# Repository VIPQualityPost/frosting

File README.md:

Small, Nucleo-64 sized carrier for icesugar pro and colorlight i9 FPGA development boards. I designed this in order to be able to use the handful of Arduino and Morpho shields I have with these dev kits to avoid needing to use weird PMODS or breadboards.

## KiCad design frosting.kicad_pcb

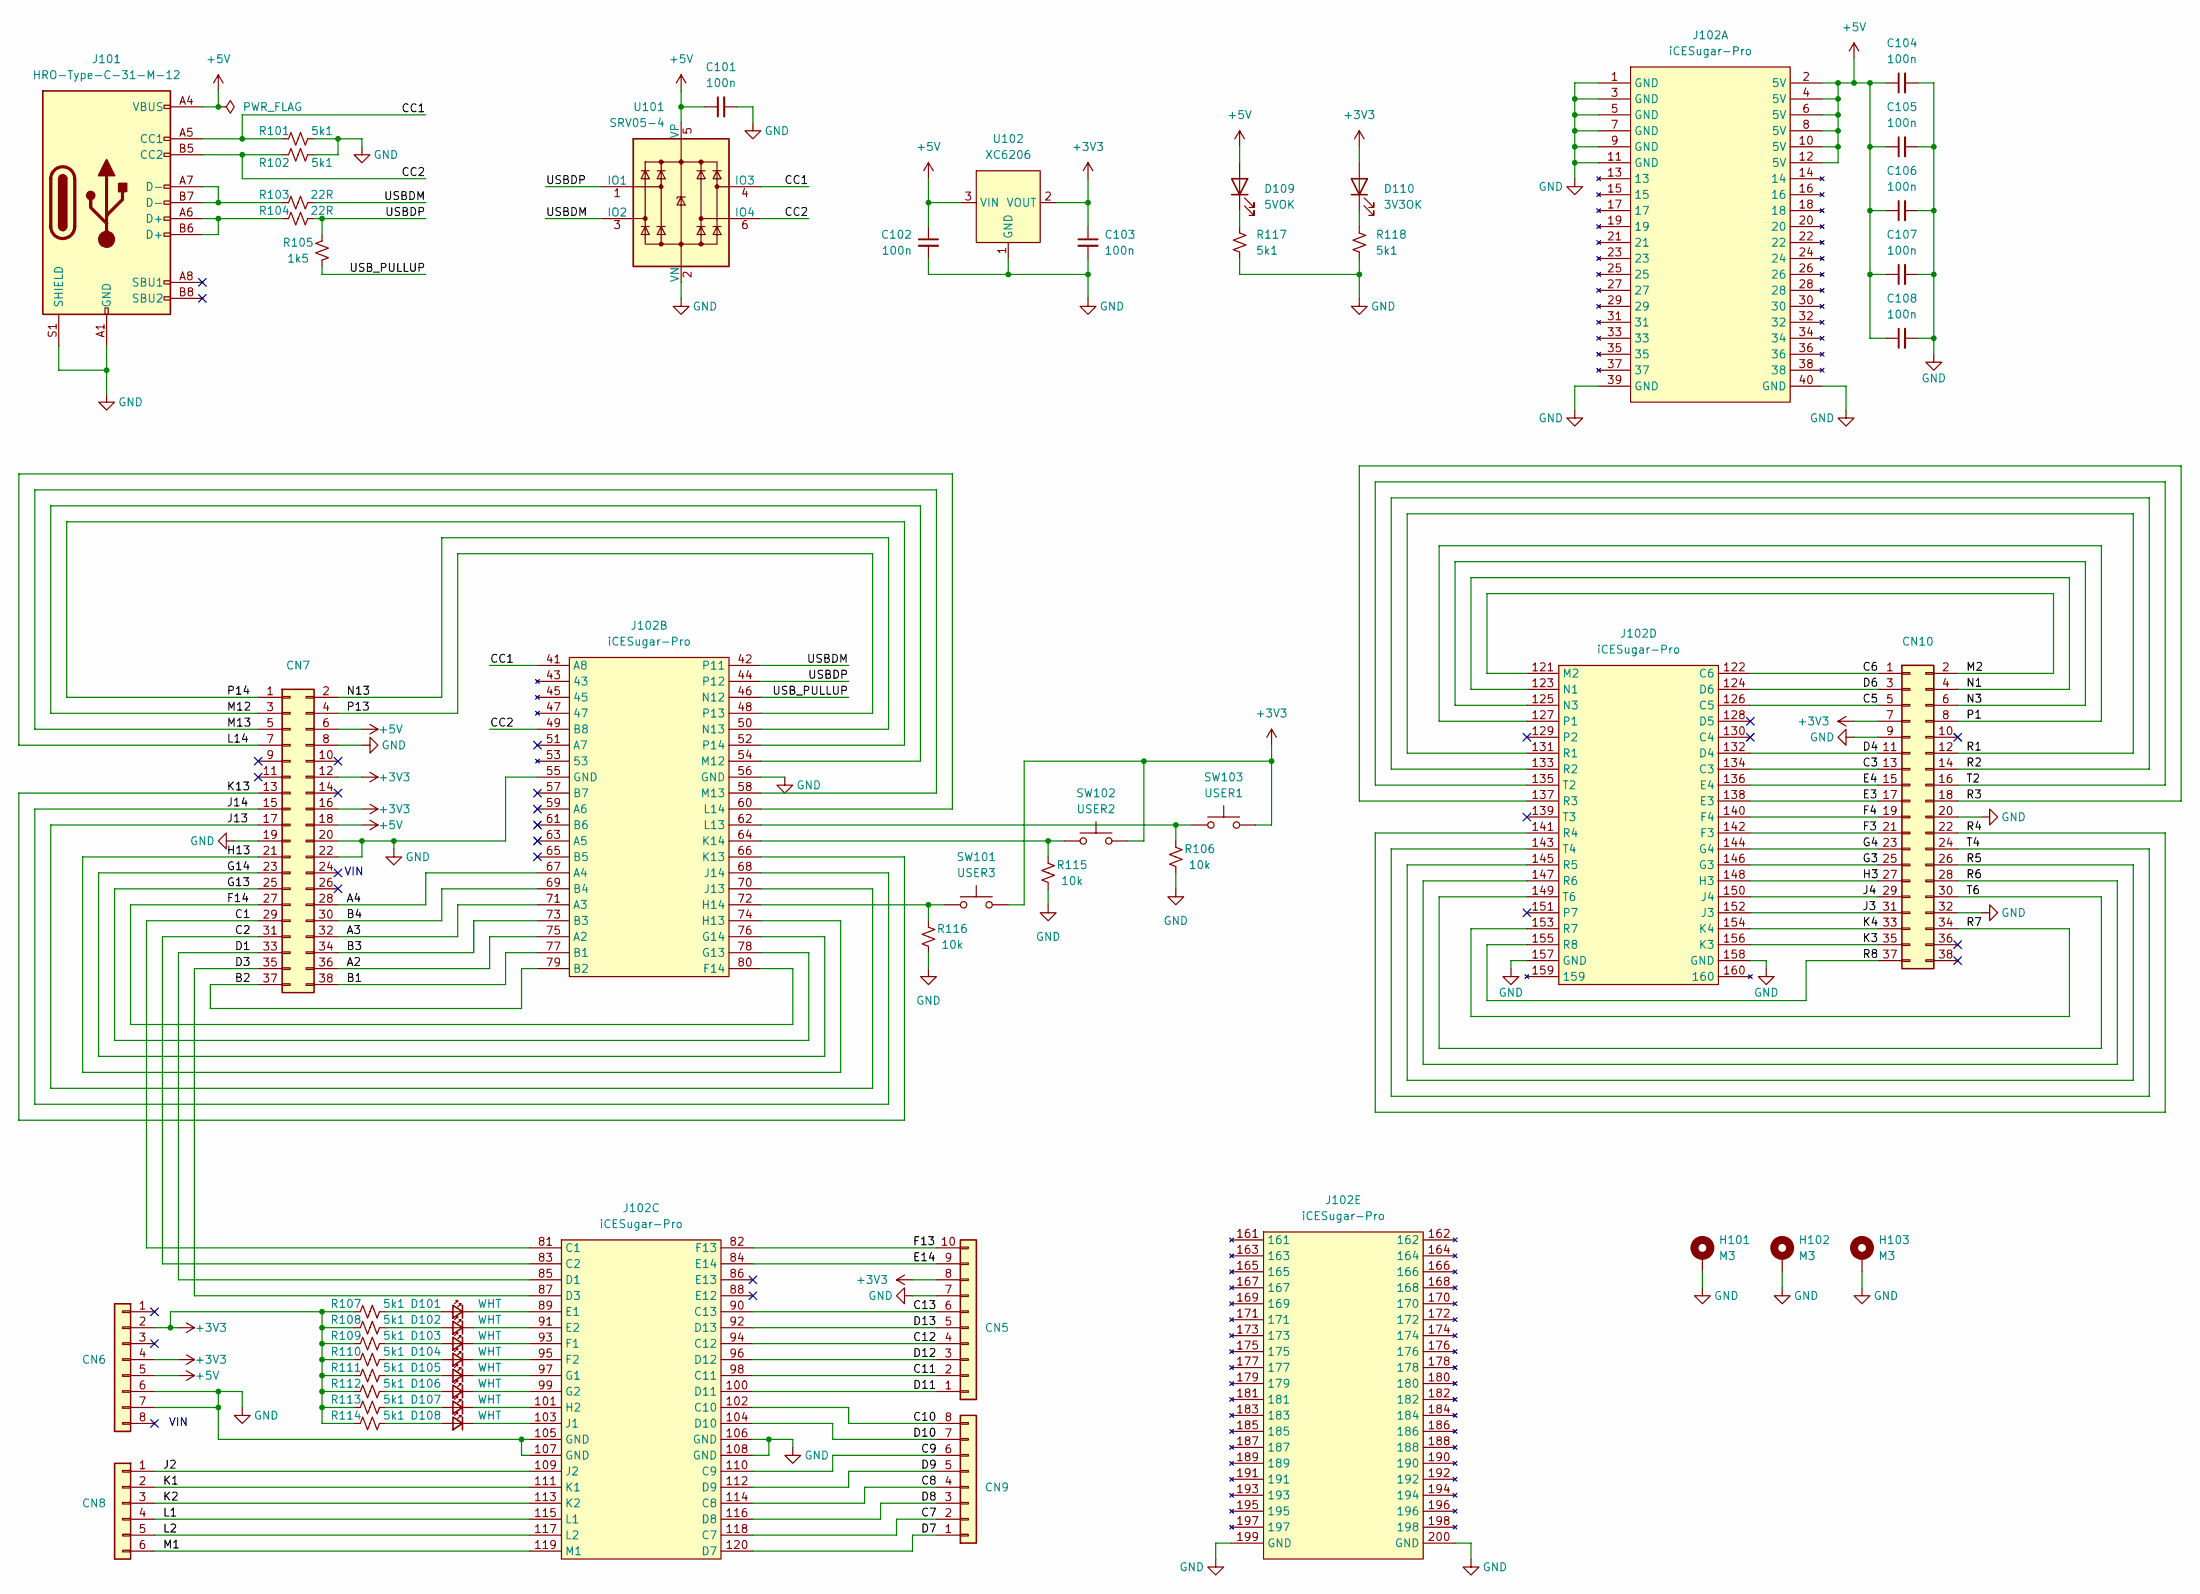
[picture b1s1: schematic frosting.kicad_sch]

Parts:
C101, C102, C103, C104, C105, C106, C107, C108: 100n; C_0402_1005Metric; LCSC ID C307331
CN5: CON_SAMTEC_SSW-110-03-X-S; LCSC ID C5116489
CN6, CN9: CON_SAMTEC_SSW-108-03-X-S; LCSC ID C27438
CN7, CN10: CON_SAMTEC_TSW-119-09-X-D; LCSC ID C2685155
CN8: CON_SAMTEC_SSW-106-03-X-S; LCSC ID C40877
D101, D102, D103, D104, D105, D106, D107, D108: WHT; LED_0603_1608Metric; LCSC ID C2290
D109: 5VOK; LED_0603_1608Metric; LCSC ID C2290
D110: 3V3OK; LED_0603_1608Metric; LCSC ID C2290
H101, H102, H103: M3; MountingHole_3.2mm_M3_DIN965_Pad
J101: HRO-Type-C-31-M-12; HRO-TYPE-C-31-M-12; LCSC ID C165948
J102: iCESugar-Pro; SO-DIMM-SMD_200P-P0.60_1473005-4; LCSC ID C428482
R101, R102, R107, R108, R109, R110, R111, R112, R113, R114, R117, R118: 5k1; R_0402_1005Metric; LCSC ID C25905
R103, R104: 22R; R_0402_1005Metric; LCSC ID C25092
R105: 1k5; R_0402_1005Metric; LCSC ID C25867
R106, R115, R116: 10k; R_0402_1005Metric; LCSC ID C25744
SW101: USER3; TS-1187A-B-A-B; LCSC ID C318884
SW102: USER2; TS-1187A-B-A-B; LCSC ID C318884
SW103: USER1; TS-1187A-B-A-B; LCSC ID C318884
U101: SRV05-4; SOT-23-6; LCSC ID C7420376
U102: XC6206; SOT-23; LCSC ID C5446

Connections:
+3V3: C103.1, CN5.8, CN6.2, CN6.4, CN7.12, CN7.16, CN10.7, D110.2 (A), R107.1, R108.1, R109.1, R110.1, R111.1, R112.1, R113.1, R114.1, SW101.2, SW102.2, SW103.2, U102.2 (VOUT)
+5V: C101.1, C102.1, C104.1, C105.1, C106.1, C107.1, C108.1, CN6.5, CN7.6, CN7.18, D109.2 (A), J101.A4 (VBUS), J101.A9 (VBUS), J101.B4 (VBUS), J101.B9 (VBUS), J102.2 (5V), J102.4 (5V), J102.6 (5V), J102.8 (5V), J102.10 (5V), J102.12 (5V), U101.5 (VP), U102.3 (VIN)
/A2: CN7.36, J102.75 (A2)
/A3: CN7.32, J102.71 (A3)
/A4: CN7.28, J102.67 (A4)
/B1: CN7.38, J102.77 (B1)
/B2: CN7.37, J102.79 (B2)
/B3: CN7.34, J102.73 (B3)
/B4: CN7.30, J102.69 (B4)
/C1: CN7.29, J102.81 (C1)
/C2: CN7.31, J102.83 (C2)
/C3: CN10.13, J102.134 (C3)
/C5: CN10.5, J102.126 (C5)
/C6: CN10.1, J102.122 (C6)
/C7: CN9.2, J102.118 (C7)
/C8: CN9.4, J102.114 (C8)
/C9: CN9.6, J102.110 (C9)
/C10: CN9.8, J102.102 (C10)
/C11: CN5.2, J102.98 (C11)
/C12: CN5.4, J102.94 (C12)
/C13: CN5.6, J102.90 (C13)
/CC1: J101.A5 (CC1), J102.41 (A8), R101.1, U101.4 (IO3)
/CC2: J101.B5 (CC2), J102.49 (B8), R102.2, U101.6 (IO4)
/D1: CN7.33, J102.85 (D1)
/D3: CN7.35, J102.87 (D3)
/D4: CN10.11, J102.132 (D4)
/D6: CN10.3, J102.124 (D6)
/D7: CN9.1, J102.120 (D7)
/D8: CN9.3, J102.116 (D8)
/D9: CN9.5, J102.112 (D9)
/D10: CN9.7, J102.104 (D10)
/D11: CN5.1, J102.100 (D11)
/D12: CN5.3, J102.96 (D12)
/D13: CN5.5, J102.92 (D13)
/E3: CN10.17, J102.138 (E3)
/E4: CN10.15, J102.136 (E4)
/E14: CN5.9, J102.84 (E14)
/F3: CN10.21, J102.142 (F3)
/F4: CN10.19, J102.140 (F4)
/F13: CN5.10, J102.82 (F13)
/F14: CN7.27, J102.80 (F14)
/G3: CN10.25, J102.146 (G3)
/G4: CN10.23, J102.144 (G4)
/G13: CN7.25, J102.78 (G13)
/G14: CN7.23, J102.76 (G14)
/H3: CN10.27, J102.148 (H3)
/H13: CN7.21, J102.74 (H13)
/J2: CN8.1, J102.109 (J2)
/J3: CN10.31, J102.152 (J3)
/J4: CN10.29, J102.150 (J4)
/J13: CN7.17, J102.70 (J13)
/J14: CN7.15, J102.68 (J14)
/K1: CN8.2, J102.111 (K1)
/K2: CN8.3, J102.113 (K2)
/K3: CN10.35, J102.156 (K3)
/K4: CN10.33, J102.154 (K4)
/K13: CN7.13, J102.66 (K13)
/L1: CN8.4, J102.115 (L1)
/L2: CN8.5, J102.117 (L2)
/L14: CN7.7, J102.60 (L14)
/M1: CN8.6, J102.119 (M1)
/M2: CN10.2, J102.121 (M2)
/M12: CN7.3, J102.54 (M12)
/M13: CN7.5, J102.58 (M13)
/N1: CN10.4, J102.123 (N1)
/N3: CN10.6, J102.125 (N3)
/N13: CN7.2, J102.50 (N13)
/P1: CN10.8, J102.127 (P1)
/P13: CN7.4, J102.48 (P13)
/P14: CN7.1, J102.52 (P14)
/R1: CN10.12, J102.131 (R1)
/R2: CN10.14, J102.133 (R2)
/R3: CN10.18, J102.137 (R3)
/R4: CN10.22, J102.141 (R4)
/R5: CN10.26, J102.145 (R5)
/R6: CN10.28, J102.147 (R6)
/R7: CN10.34, J102.153 (R7)
/R8: CN10.37, J102.155 (R8)
/T2: CN10.16, J102.135 (T2)
/T4: CN10.24, J102.143 (T4)
/T6: CN10.30, J102.149 (T6)
/USBDM: J102.42 (P11), R103.2, U101.3 (IO2)
/USBDP: J102.44 (P12), R104.1, R105.1, U101.1 (IO1)
/USB_PULLUP: J102.46 (N12), R105.2
GND: C101.2, C102.2, C103.2, C104.2, C105.2, C106.2, C107.2, C108.2, CN5.7, CN6.6, CN6.7, CN7.8, CN7.19, CN7.20, CN7.22, CN10.9, CN10.20, CN10.32, H101.1, H102.1, H103.1, J101.A1 (GND), J101.A12 (GND), J101.B1 (GND), J101.B12 (GND), J101.S1 (SHIELD), J102.1 (GND), J102.3 (GND), J102.5 (GND), J102.7 (GND), J102.9 (GND), J102.11 (GND), J102.39 (GND), J102.40 (GND), J102.55 (GND), J102.56 (GND), J102.105 (GND), J102.106 (GND), J102.107 (GND), J102.108 (GND), J102.157 (GND), J102.158 (GND), J102.199 (GND), J102.200 (GND), R101.2, R102.1, R106.2, R115.2, R116.2, R117.2, R118.2, U101.2 (VN), U102.1 (GND)
unnamed: D101.2 (A), R107.2
unnamed: D101.1 (K), J102.89 (E1)
unnamed: D102.2 (A), R108.2
unnamed: D102.1 (K), J102.91 (E2)
unnamed: D103.2 (A), R109.2
unnamed: D103.1 (K), J102.93 (F1)
unnamed: D104.2 (A), R110.2
unnamed: D104.1 (K), J102.95 (F2)
unnamed: D105.2 (A), R111.2
unnamed: D105.1 (K), J102.97 (G1)
unnamed: D106.2 (A), R112.2
unnamed: D106.1 (K), J102.99 (G2)
unnamed: D107.2 (A), R113.2
unnamed: D107.1 (K), J102.101 (H2)
unnamed: D108.2 (A), R114.2
unnamed: D108.1 (K), J102.103 (J1)
unnamed: D109.1 (K), R117.1
unnamed: D110.1 (K), R118.1
unnamed: J101.A6 (D+), J101.B6 (D+), R104.2
unnamed: J101.A7 (D-), J101.B7 (D-), R103.1
unnamed: J102.72 (H14), R116.1, SW101.1
unnamed: J102.64 (K14), R115.1, SW102.1
unnamed: J102.62 (L13), R106.1, SW103.1

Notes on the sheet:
VIN

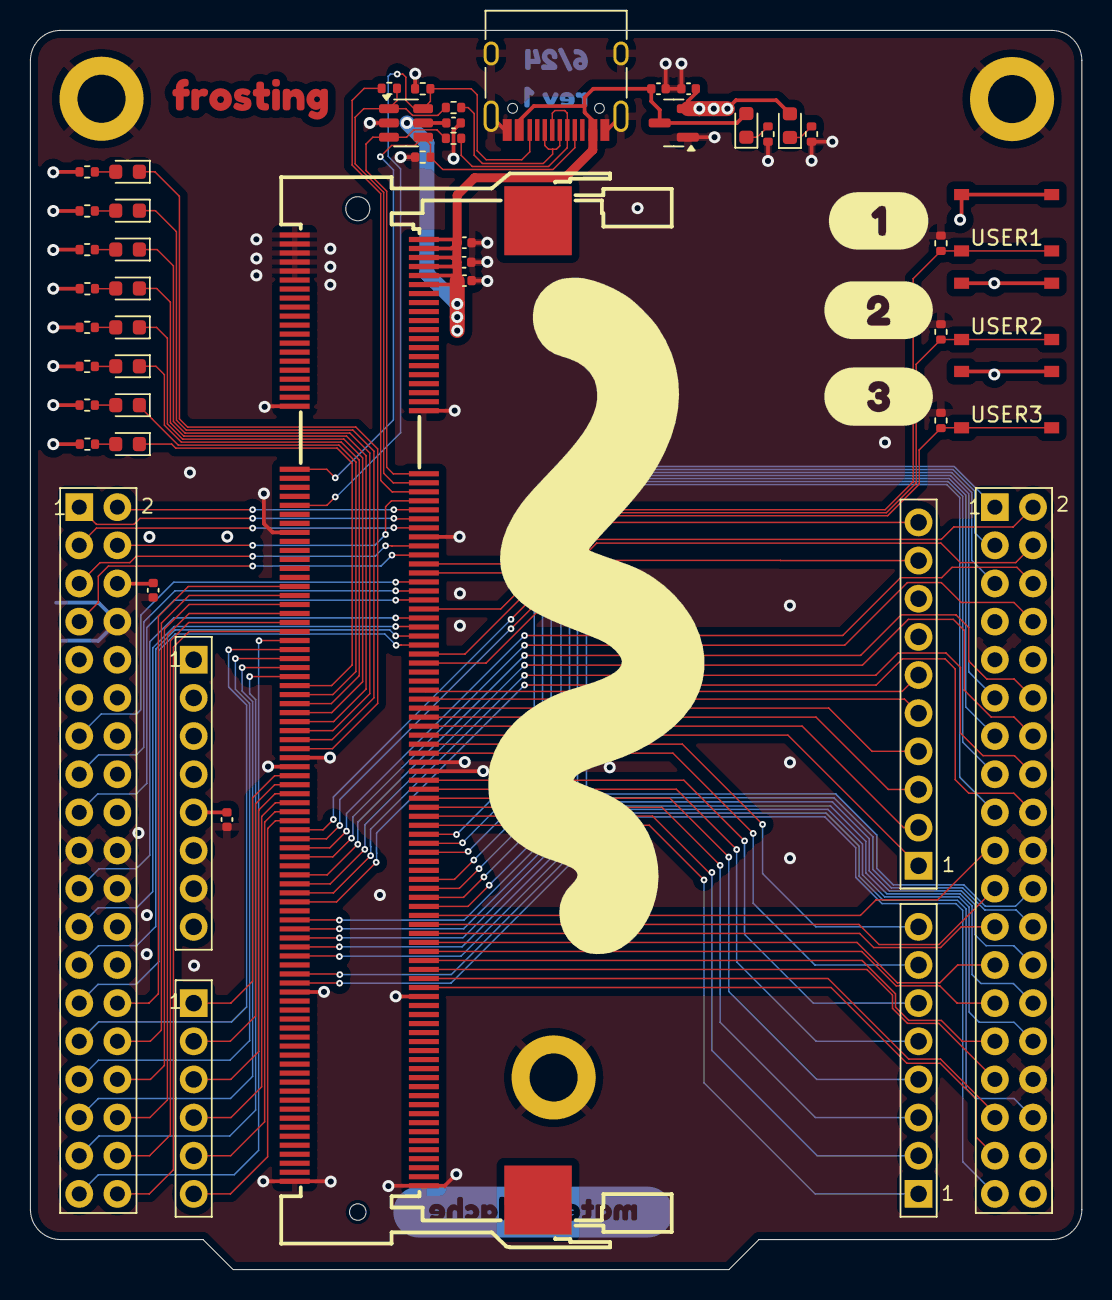
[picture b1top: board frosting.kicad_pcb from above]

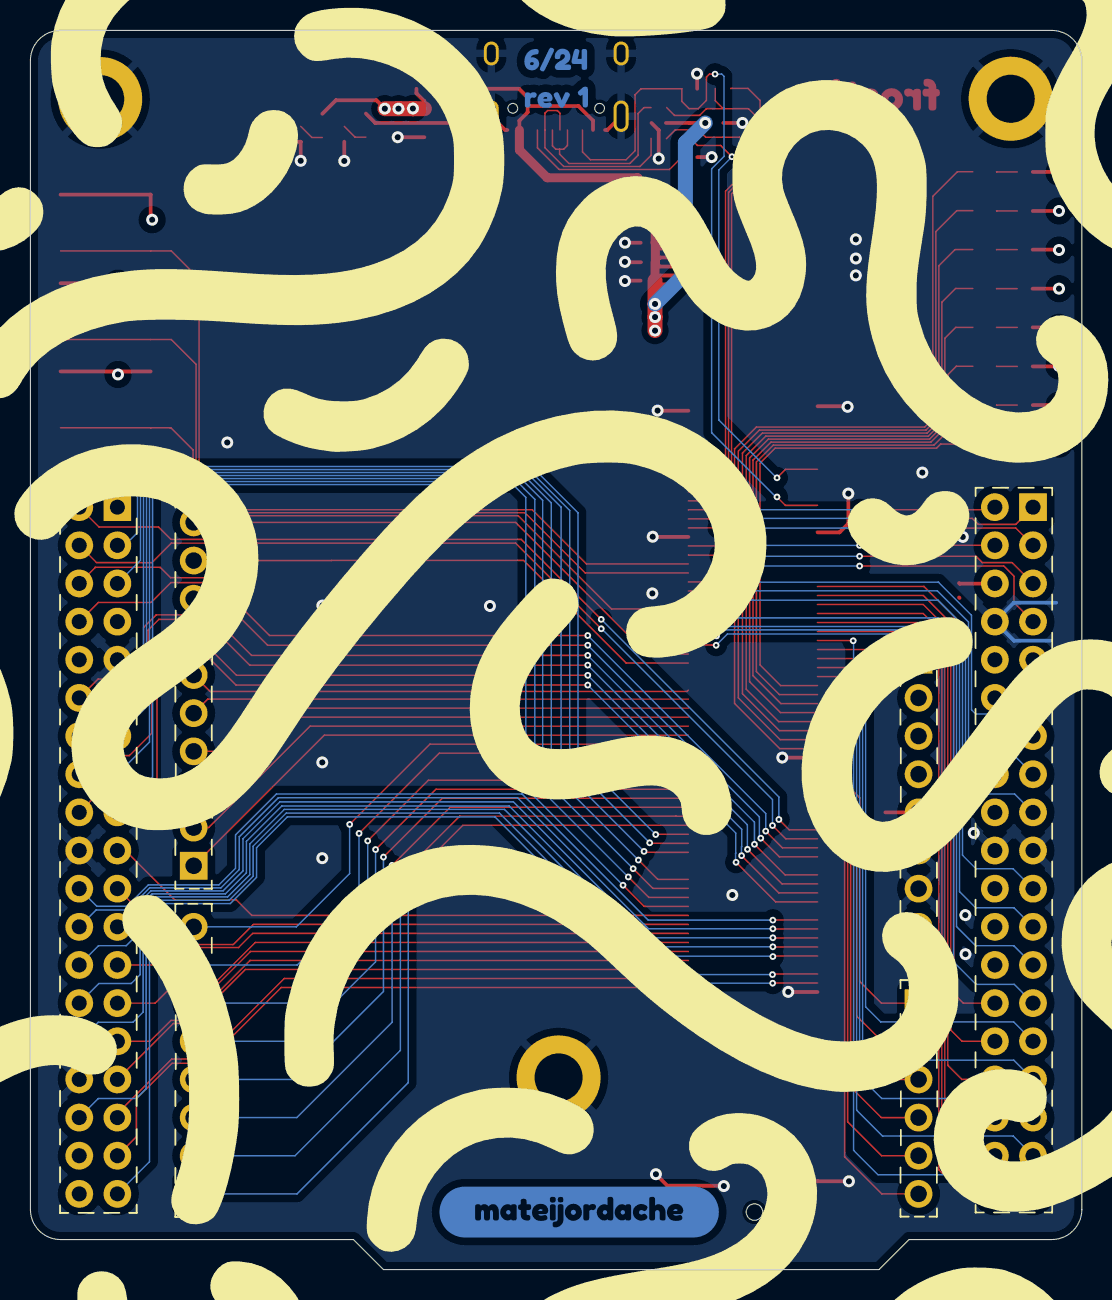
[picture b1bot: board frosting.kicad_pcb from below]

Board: 4 copper layers, 70.0 x 82.5 mm, 58 parts (2 on the bottom side), 108 nets.

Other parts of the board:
kibuzzard-665D4EF8: G***; kibuzzard-665D4EF8
kibuzzard-665D4EFE: G***; kibuzzard-665D4EFE
kibuzzard-665D4F04: G***; kibuzzard-665D4F04
kibuzzard-665D4F76: G***; kibuzzard-665D4F76
kibuzzard-665D4FC5: G***; kibuzzard-665D4FC5
kibuzzard-665D501B: G***; kibuzzard-665D501B

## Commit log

2024-06-03 Add in workflow scripts
2024-06-04 clean erc drc
2024-06-04 Add design file PDFs to repo [skip ci]
2024-06-04 mask silk
2024-06-06 update grid origin and change 1x10P PN
2024-06-06 Update layer names
2024-06-13 Fix missing edge cuts
